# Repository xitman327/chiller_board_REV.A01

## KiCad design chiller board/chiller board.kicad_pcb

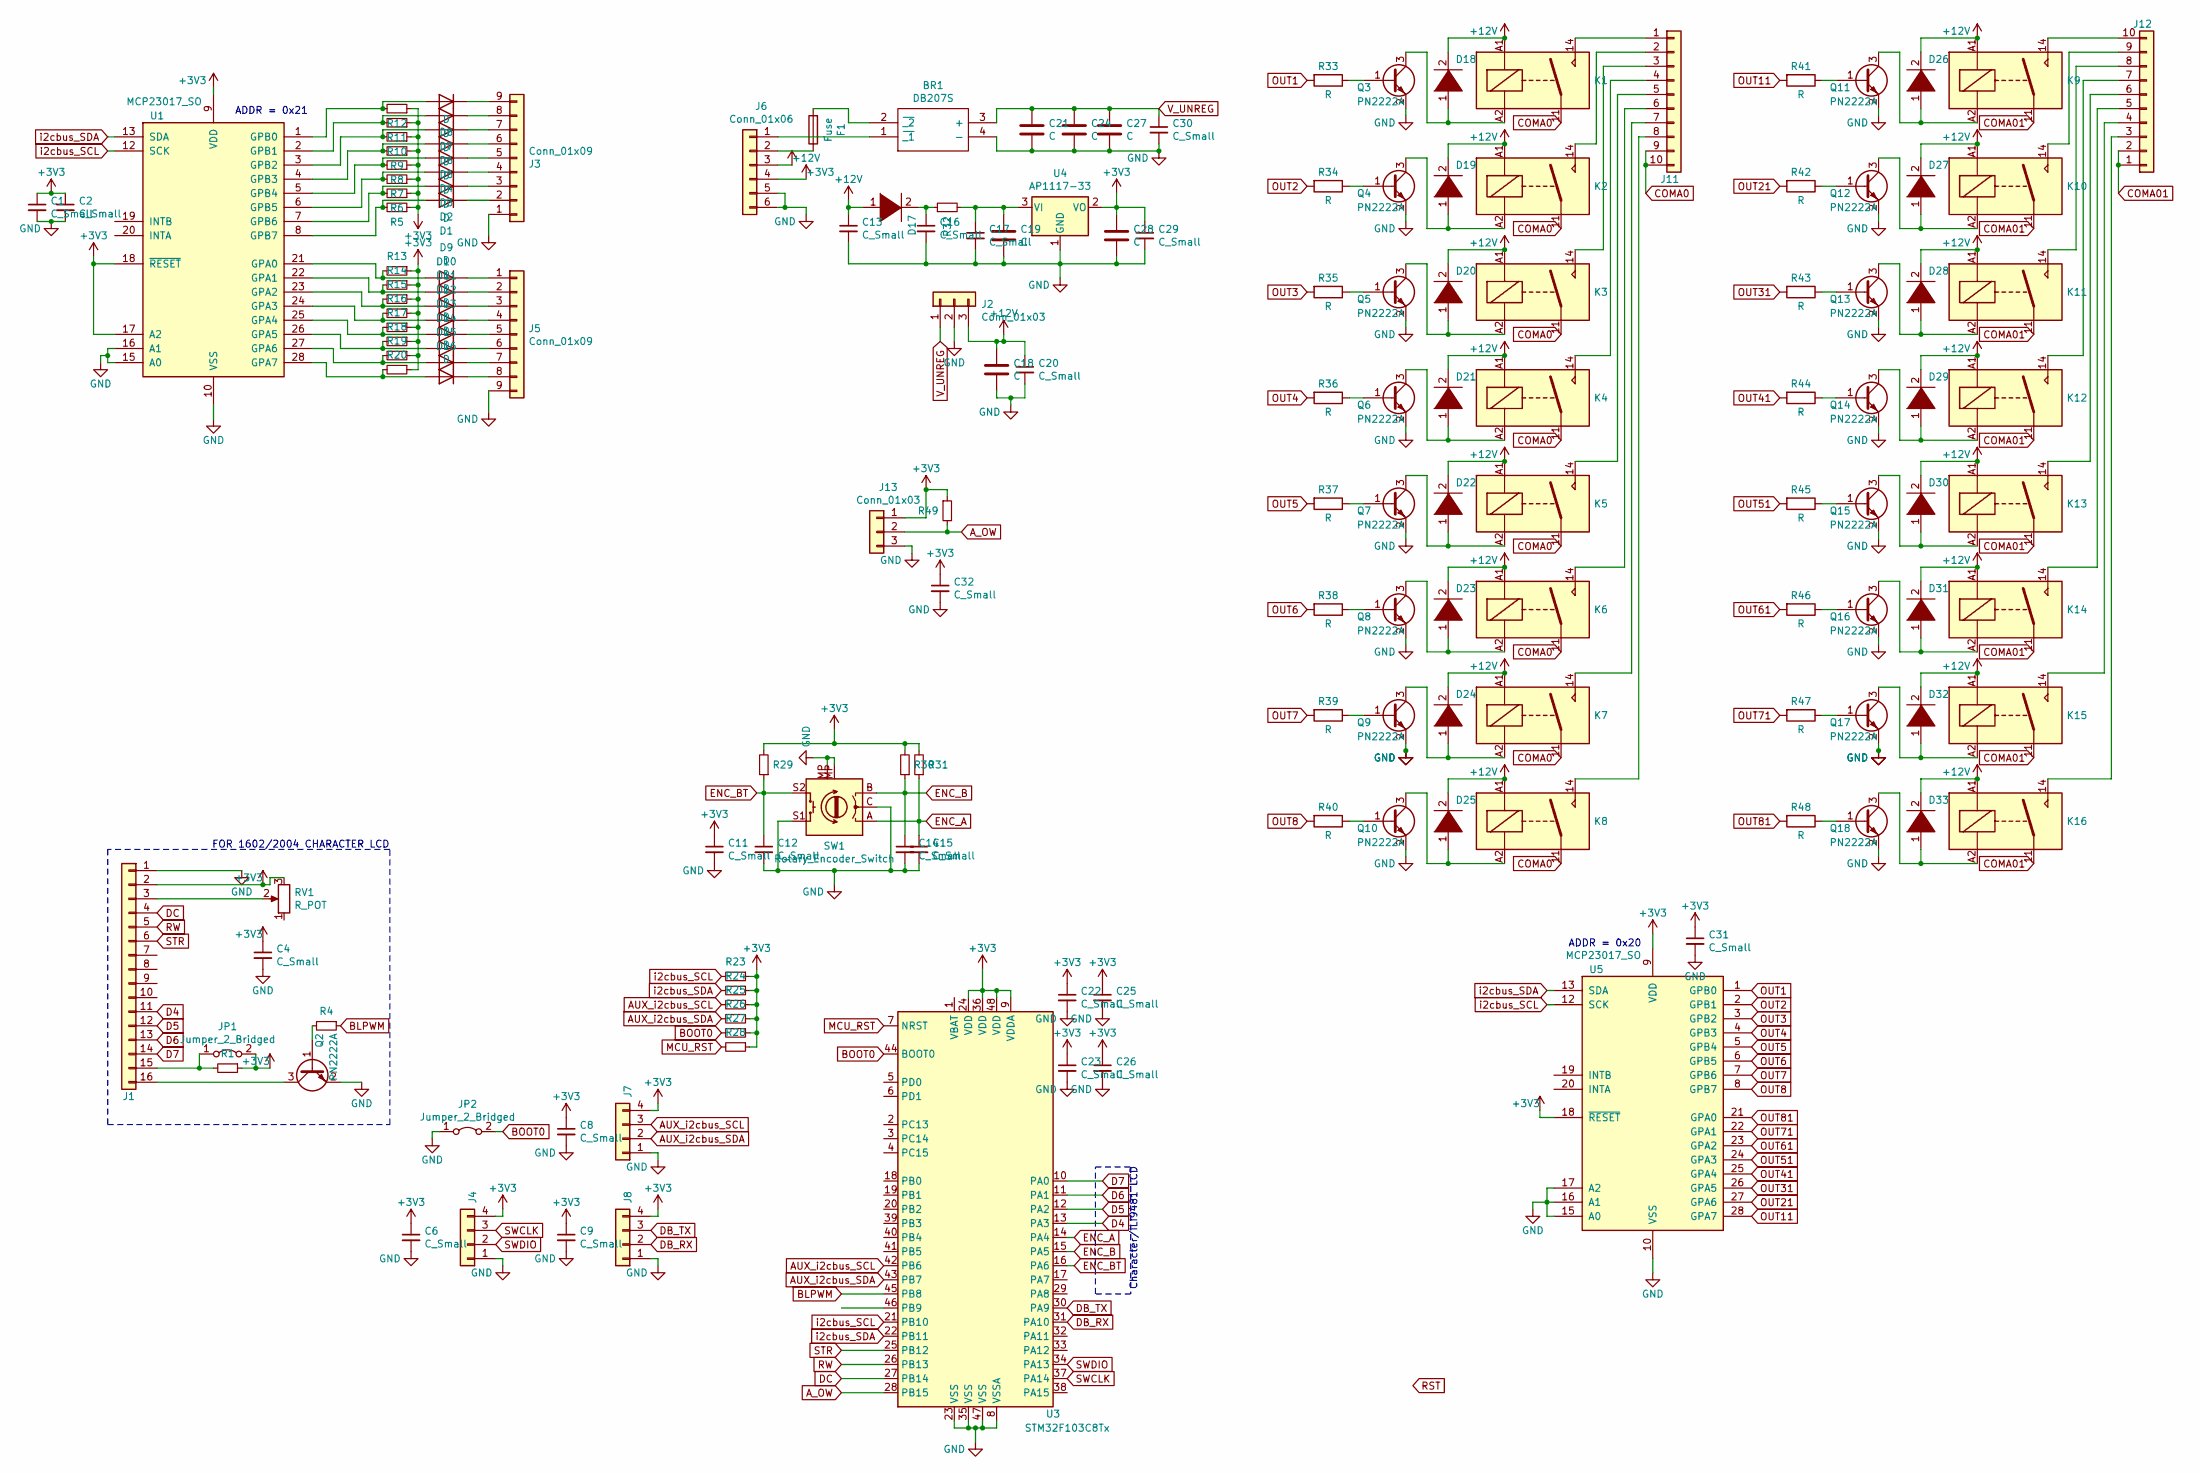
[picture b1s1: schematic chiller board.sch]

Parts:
BR1: DB207S; SOP510P1015X375-4N; Manufacturer_Part_Number DB207S
C1, C2, C4, C6, C8, C9, C11, C12, C13, C14, C15, C16, C17, C20, C22, C23, C25, C26, C32: C_Small; C_0805_2012Metric
C18, C19, C21, C24, C27, C28: C; CP_Radial_D10.0mm_P7.50mm
C29, C30, C31: C_Small; C_0603_1608Metric
D1, D2, D3, D4, D5, D6, D7, D8, D9, D10, D11, D12, D13, D14, D15, D16: D; D_MELF
D17, D18, D19, D20, D21, D22, D23, D24, D25, D26, D27, D28, D29, D30, D31, D32, D33: DIODE; D_MELF
F1: Fuse; Fuse_1206_3216Metric
J1: Conn_01x16; LCD-16x2
J2: Conn_01x03; PinHeader_1x03_P2.54mm_Vertical
J3, J5: Conn_01x09; TerminalBlock_Phoenix_MKDS-1,5-9_1x09_P5.00mm_Horizontal
J4, J7, J8: Conn_01x04; PinHeader_1x04_P2.54mm_Vertical
J6: Conn_01x06; TerminalBlock_Phoenix_MKDS-1,5-6_1x06_P5.00mm_Horizontal
J11, J12: Conn_01x10; TerminalBlock_Phoenix_MKDS-1,5-10_1x10_P5.00mm_Horizontal
J13: Conn_01x03; TerminalBlock_Phoenix_MKDS-1,5-3_1x03_P5.00mm_Horizontal
JP1, JP2: Jumper_2_Bridged; SolderJumper-2_P1.3mm_Open_Pad1.0x1.5mm
K1, K2, K3, K4, K5, K6, K7, K8, K9, K10, K11, K12, K13, K14, K15, K16: FINDER-36.11-4301; APAN3112
Q2, Q3, Q4, Q5, Q6, Q7, Q8, Q9, Q10, Q11, Q12, Q13, Q14, Q15, Q16, Q17, Q18: PN2222A; SOT-23
R1, R4, R5, R6, R7, R8, R9, R10, R11, R12, R13, R14, R15, R16, R17, R18, R19, R20, R23, R24, R25, R26, R27, R28, R29, R30, R31, R32, R49: R_Small; R_0603_1608Metric
R33, R34, R35, R36, R37, R38, R39, R40, R41, R42, R43, R44, R45, R46, R47, R48: R; R_0603_1608Metric
RV1: R_POT; Potentiometer_ACP_CA9-H2,5_Horizontal
SW1: Rotary_Encoder_Switch; RotaryEncoder_Alps_EC11E-Switch_Vertical_H20mm
U1, U5: MCP23017_SO; SSOP-28_5.3x10.2mm_P0.65mm
U3: STM32F103C8Tx; LQFP-48_7x7mm_P0.5mm
U4: AP1117-33; SOT-223-3_TabPin2

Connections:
+3V3: C1.1, C2.1, C4.1, C6.1, C8.1, C9.1, C11.1, C22.1, C23.1, C25.1, C26.1, C28.1, C29.1, C31.1, C32.1, J1.2, J4.4, J6.4, J7.4, J8.4, J13.1, JP1.2 (B), R1.1, R5.1, R6.1, R7.1, R8.1, R9.1, R10.1, R11.1, R12.1, R13.1, R14.1, R15.1, R16.1, R17.1, R18.1, R19.1, R20.1, R23.1, R24.1, R25.1, R26.1, R27.1, R28.1, R29.2, R30.2, R31.2, R49.1, RV1.3, U1.9 (VDD), U1.17 (A2), U1.18 (~RESET~), U3.9 (VDDA), U3.24 (VDD), U3.36 (VDD), U3.48 (VDD), U4.2 (VO), U5.9 (VDD), U5.18 (~RESET~)
+12V: C13.1, C18.1, C20.1, D17.1 (K), D18.2 (A), D19.2 (A), D20.2 (A), D21.2 (A), D22.2 (A), D23.2 (A), D24.2 (A), D25.2 (A), D26.2 (A), D27.2 (A), D28.2 (A), D29.2 (A), D30.2 (A), D31.2 (A), D32.2 (A), D33.2 (A), J2.3, J6.3, K1.A1, K2.A1, K3.A1, K4.A1, K5.A1, K6.A1, K7.A1, K8.A1, K9.A1, K10.A1, K11.A1, K12.A1, K13.A1, K14.A1, K15.A1, K16.A1
AUX_i2cbus_SCL: J7.3, R25.2, U3.42 (PB6)
AUX_i2cbus_SDA: J7.2, R26.2, U3.43 (PB7)
A_OW: J13.2, R49.2, U3.28 (PB15)
BLPWM: R4.1, U3.45 (PB8)
BOOT0: JP2.2 (B), R27.2, U3.44 (BOOT0)
COMA0: J11.9, J11.10, K1.11, K2.11, K3.11, K4.11, K5.11, K6.11, K7.11, K8.11
COMA01: J12.1, J12.2, K9.11, K10.11, K11.11, K12.11, K13.11, K14.11, K15.11, K16.11
D4: J1.11, U3.13 (PA3)
D5: J1.12, U3.12 (PA2)
D6: J1.13, U3.11 (PA1)
D7: J1.14, U3.10 (PA0)
DB_RX: J8.2, U3.31 (PA10)
DB_TX: J8.3, U3.30 (PA9)
DC: J1.4, U3.27 (PB14)
ENC_A: C15.1, R31.1, SW1.A, U3.14 (PA4)
ENC_B: C14.1, R30.1, SW1.B, U3.15 (PA5)
ENC_BT: C12.1, R29.1, SW1.S2, U3.16 (PA6)
GND: BR1.4 (-), C1.2, C2.2, C4.2, C6.2, C8.2, C9.2, C11.2, C12.2, C13.2, C14.2, C15.2, C16.2, C17.2, C18.2, C19.2, C20.2, C21.2, C22.2, C23.2, C24.2, C25.2, C26.2, C27.2, C28.2, C29.2, C30.2, C31.2, C32.2, J1.1, J2.2, J3.1, J4.1, J5.9, J6.5, J6.6, J7.1, J8.1, J13.3, JP2.1 (A), Q2.2 (E), Q3.2 (E), Q4.2 (E), Q5.2 (E), Q6.2 (E), Q7.2 (E), Q8.2 (E), Q9.2 (E), Q10.2 (E), Q11.2 (E), Q12.2 (E), Q13.2 (E), Q14.2 (E), Q15.2 (E), Q16.2 (E), Q17.2 (E), Q18.2 (E), SW1.C, SW1.MP, SW1.S1, U1.10 (VSS), U1.15 (A0), U1.16 (A1), U3.8 (VSSA), U3.23 (VSS), U3.35 (VSS), U3.47 (VSS), U4.1 (GND), U5.10 (VSS), U5.15 (A0), U5.16 (A1), U5.17 (A2)
MCU_RST: R28.2, U3.7 (NRST)
unnamed: BR1.1 (~_1), J6.1
unnamed: BR1.2 (~_2), F1.2
unnamed: C16.1, D17.2 (A), R32.1
unnamed: C17.1, C19.1, R32.2, U4.3 (VI)
unnamed: D1.1 (K), J3.2
unnamed: D1.2 (A), R5.2, U1.8 (GPB7)
unnamed: D2.1 (K), J3.3
unnamed: D2.2 (A), R6.2, U1.7 (GPB6)
unnamed: D3.1 (K), J3.4
unnamed: D3.2 (A), R7.2, U1.6 (GPB5)
unnamed: D4.1 (K), J3.5
unnamed: D4.2 (A), R8.2, U1.5 (GPB4)
unnamed: D5.1 (K), J3.6
unnamed: D5.2 (A), R9.2, U1.4 (GPB3)
unnamed: D6.1 (K), J3.7
unnamed: D6.2 (A), R10.2, U1.3 (GPB2)
unnamed: D7.1 (K), J3.8
unnamed: D7.2 (A), R11.2, U1.2 (GPB1)
unnamed: D8.1 (K), J3.9
unnamed: D8.2 (A), R12.2, U1.1 (GPB0)
unnamed: D9.1 (K), J5.1
unnamed: D9.2 (A), R13.2, U1.21 (GPA0)
unnamed: D10.1 (K), J5.2
unnamed: D10.2 (A), R14.2, U1.22 (GPA1)
unnamed: D11.1 (K), J5.3
unnamed: D11.2 (A), R15.2, U1.23 (GPA2)
unnamed: D12.1 (K), J5.4
unnamed: D12.2 (A), R16.2, U1.24 (GPA3)
unnamed: D13.1 (K), J5.5
unnamed: D13.2 (A), R17.2, U1.25 (GPA4)
unnamed: D14.1 (K), J5.6
unnamed: D14.2 (A), R18.2, U1.26 (GPA5)
unnamed: D15.1 (K), J5.7
unnamed: D15.2 (A), R19.2, U1.27 (GPA6)
unnamed: D16.1 (K), J5.8
unnamed: D16.2 (A), R20.2, U1.28 (GPA7)
unnamed: D18.1 (K), K1.A2, Q3.3 (C)
unnamed: D19.1 (K), K2.A2, Q4.3 (C)
unnamed: D20.1 (K), K3.A2, Q5.3 (C)
unnamed: D21.1 (K), K4.A2, Q6.3 (C)
unnamed: D22.1 (K), K5.A2, Q7.3 (C)
unnamed: D23.1 (K), K6.A2, Q8.3 (C)
unnamed: D24.1 (K), K7.A2, Q9.3 (C)
unnamed: D25.1 (K), K8.A2, Q10.3 (C)
unnamed: D26.1 (K), K9.A2, Q11.3 (C)
unnamed: D27.1 (K), K10.A2, Q12.3 (C)
unnamed: D28.1 (K), K11.A2, Q13.3 (C)
unnamed: D29.1 (K), K12.A2, Q14.3 (C)
unnamed: D30.1 (K), K13.A2, Q15.3 (C)
unnamed: D31.1 (K), K14.A2, Q16.3 (C)
unnamed: D32.1 (K), K15.A2, Q17.3 (C)
unnamed: D33.1 (K), K16.A2, Q18.3 (C)
unnamed: F1.1, J6.2
unnamed: J1.3, RV1.2
unnamed: J1.15, JP1.1 (A), R1.2
unnamed: J1.16, Q2.3 (C)
unnamed: J11.1, K1.14
unnamed: J11.2, K2.14
unnamed: J11.3, K3.14
unnamed: J11.4, K4.14
unnamed: J11.5, K5.14
unnamed: J11.6, K6.14
unnamed: J11.7, K7.14
unnamed: J11.8, K8.14
unnamed: J12.3, K16.14
unnamed: J12.4, K15.14
unnamed: J12.5, K14.14
unnamed: J12.6, K13.14
unnamed: J12.7, K12.14
unnamed: J12.8, K11.14
unnamed: J12.9, K10.14
unnamed: J12.10, K9.14
unnamed: Q2.1 (B), R4.2
unnamed: Q3.1 (B), R33.1
unnamed: Q4.1 (B), R34.1
unnamed: Q5.1 (B), R35.1
unnamed: Q6.1 (B), R36.1
unnamed: Q7.1 (B), R37.1
unnamed: Q8.1 (B), R38.1
unnamed: Q9.1 (B), R39.1
unnamed: Q10.1 (B), R40.1
unnamed: Q11.1 (B), R41.1
unnamed: Q12.1 (B), R42.1
unnamed: Q13.1 (B), R43.1
unnamed: Q14.1 (B), R44.1
unnamed: Q15.1 (B), R45.1
unnamed: Q16.1 (B), R46.1
unnamed: Q17.1 (B), R47.1
unnamed: Q18.1 (B), R48.1
OUT1: R33.2, U5.1 (GPB0)
OUT2: R34.2, U5.2 (GPB1)
OUT3: R35.2, U5.3 (GPB2)
OUT4: R36.2, U5.4 (GPB3)
OUT5: R37.2, U5.5 (GPB4)
OUT6: R38.2, U5.6 (GPB5)
OUT7: R39.2, U5.7 (GPB6)
OUT8: R40.2, U5.8 (GPB7)
OUT11: R41.2, U5.28 (GPA7)
OUT21: R42.2, U5.27 (GPA6)
OUT31: R43.2, U5.26 (GPA5)
OUT41: R44.2, U5.25 (GPA4)
OUT51: R45.2, U5.24 (GPA3)
OUT61: R46.2, U5.23 (GPA2)
OUT71: R47.2, U5.22 (GPA1)
OUT81: R48.2, U5.21 (GPA0)
RW: J1.5, U3.26 (PB13)
STR: J1.6, U3.25 (PB12)
SWCLK: J4.3, U3.37 (PA14)
SWDIO: J4.2, U3.34 (PA13)
V_UNREG: BR1.3 (+), C21.1, C24.1, C27.1, C30.1, J2.1
i2cbus_SCL: R23.2, U1.12 (SCK), U3.21 (PB10), U5.12 (SCK)
i2cbus_SDA: R24.2, U1.13 (SDA), U3.22 (PB11), U5.13 (SDA)

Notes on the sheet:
ADDR = 0x20
ADDR = 0x21
FOR 1602/2004 CHARACTER LCD
Character/ILI9481 LCD

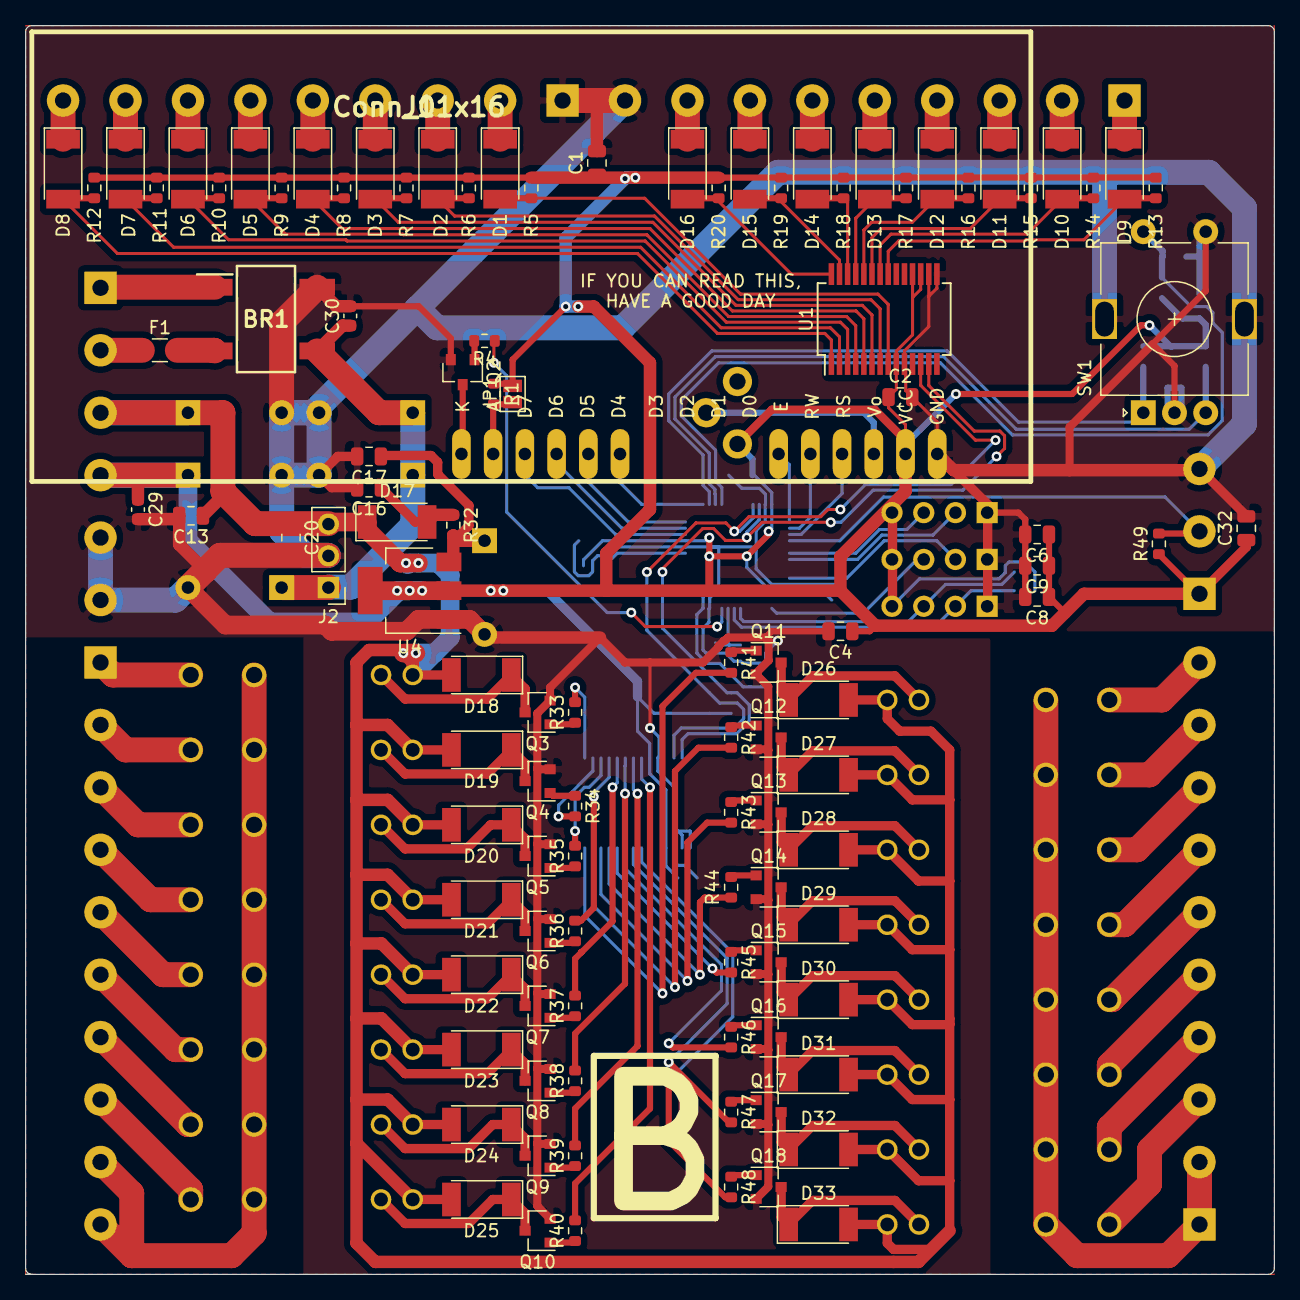
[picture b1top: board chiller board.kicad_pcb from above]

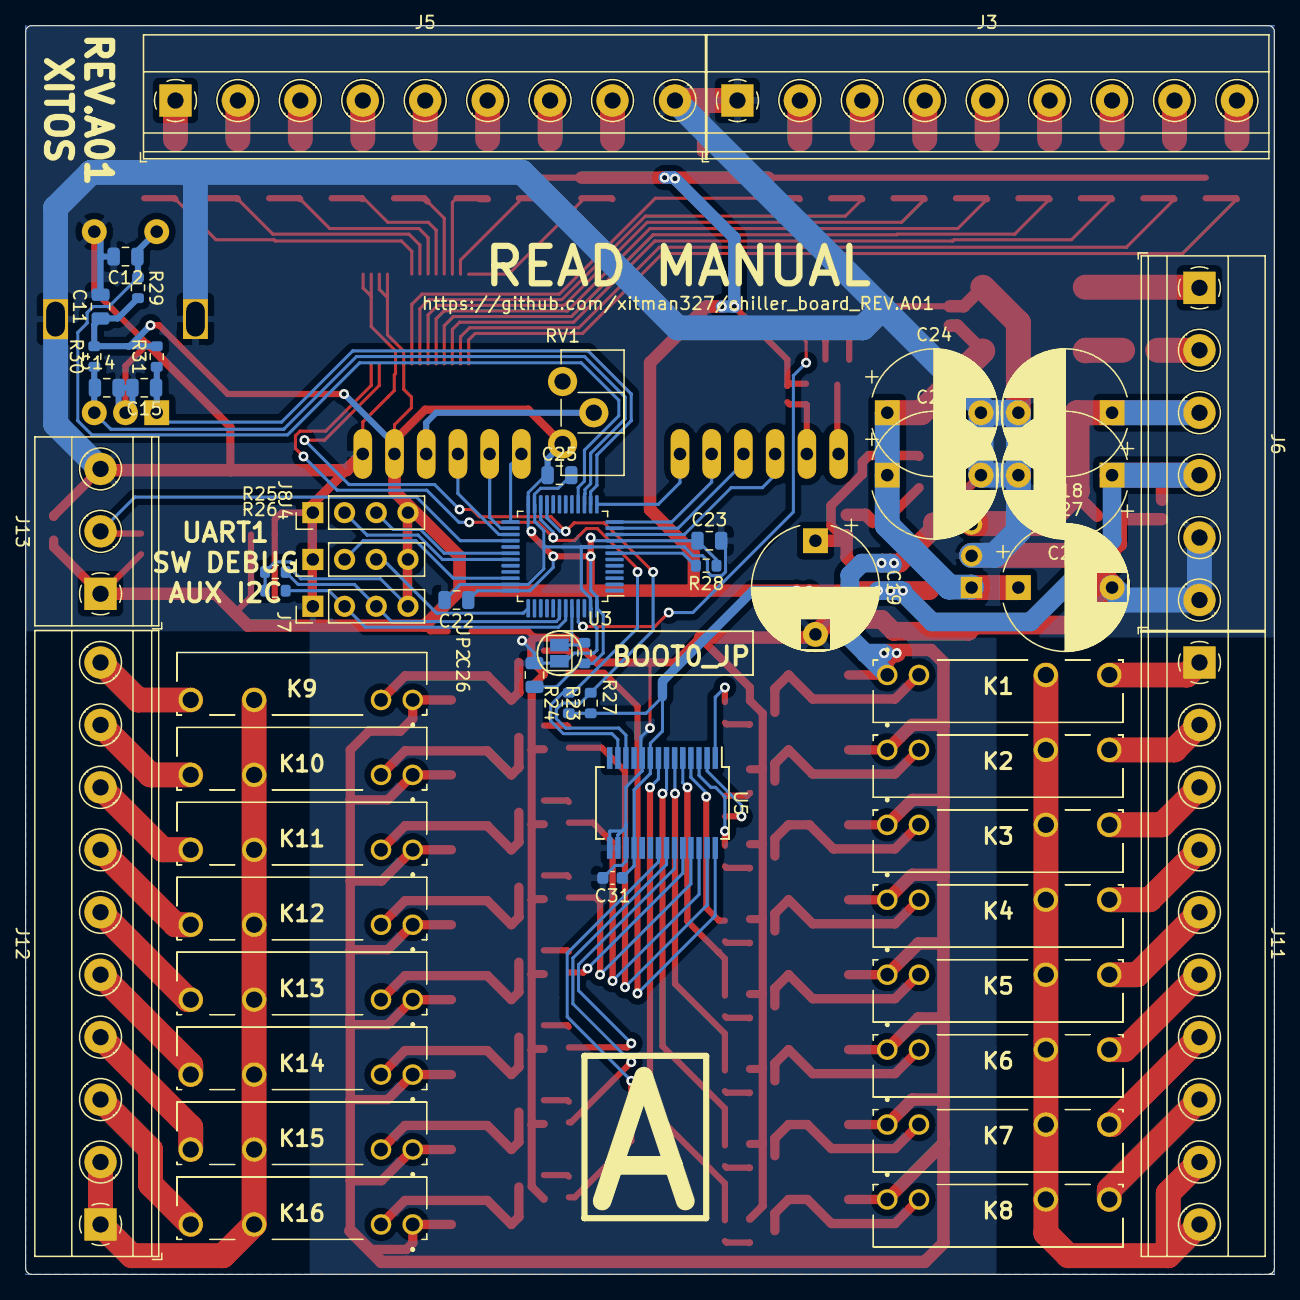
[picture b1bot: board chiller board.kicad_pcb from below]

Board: 2 copper layers, 100.0 x 100.0 mm, 160 parts (53 on the bottom side), 133 nets.
